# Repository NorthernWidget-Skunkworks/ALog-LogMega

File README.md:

ALog-LogMega
============

v. 0.8.3
rev 2

Arduino Mega (ATmega 2560) version of the ALog, designed to accomodate a larger numbers of sensors, break out a more significant set of 3.3V I/O pins, include switched VCC output, include headers for Arduino shields with switched power (e.g., for telemetry), break out SPI, I2C, and UART for communications with a wider range of sensors (and more reliable UART communications than the Software Serial library), and handle a much larger code base.

NOTE:
Gerbers out of date!
BoM out of date!

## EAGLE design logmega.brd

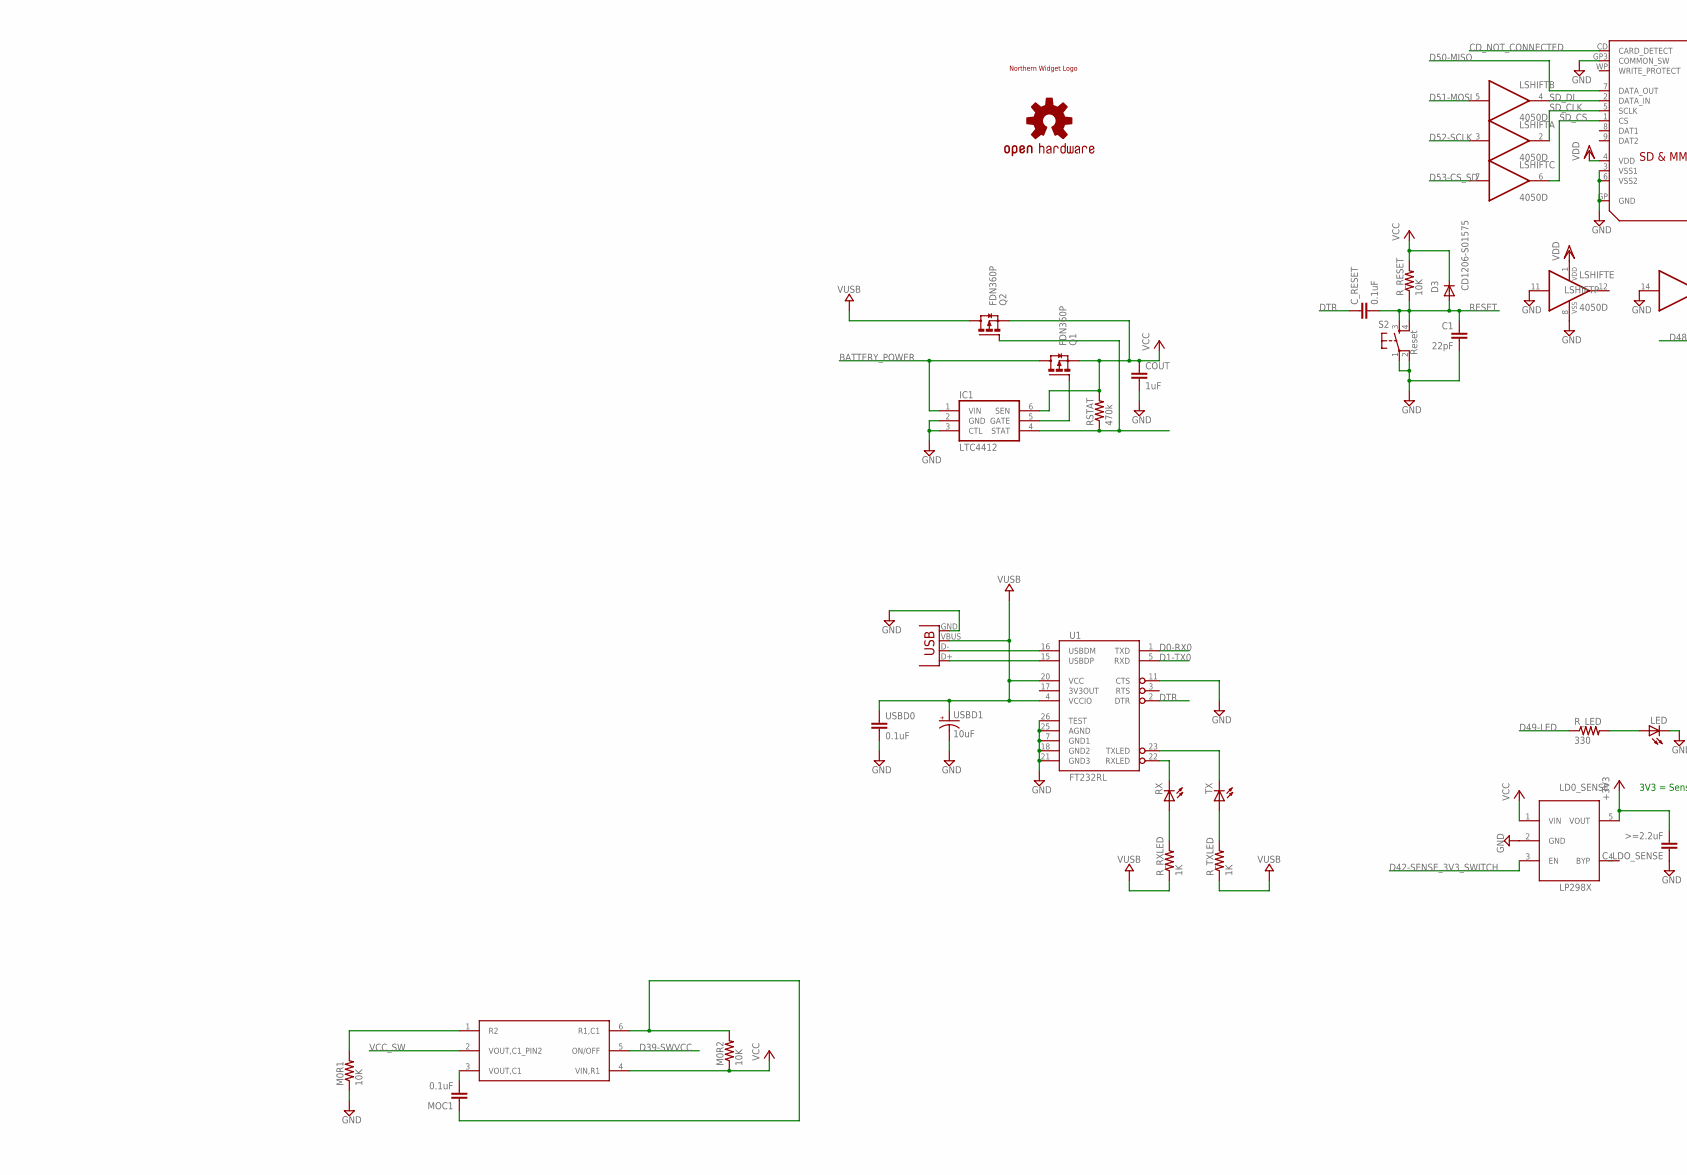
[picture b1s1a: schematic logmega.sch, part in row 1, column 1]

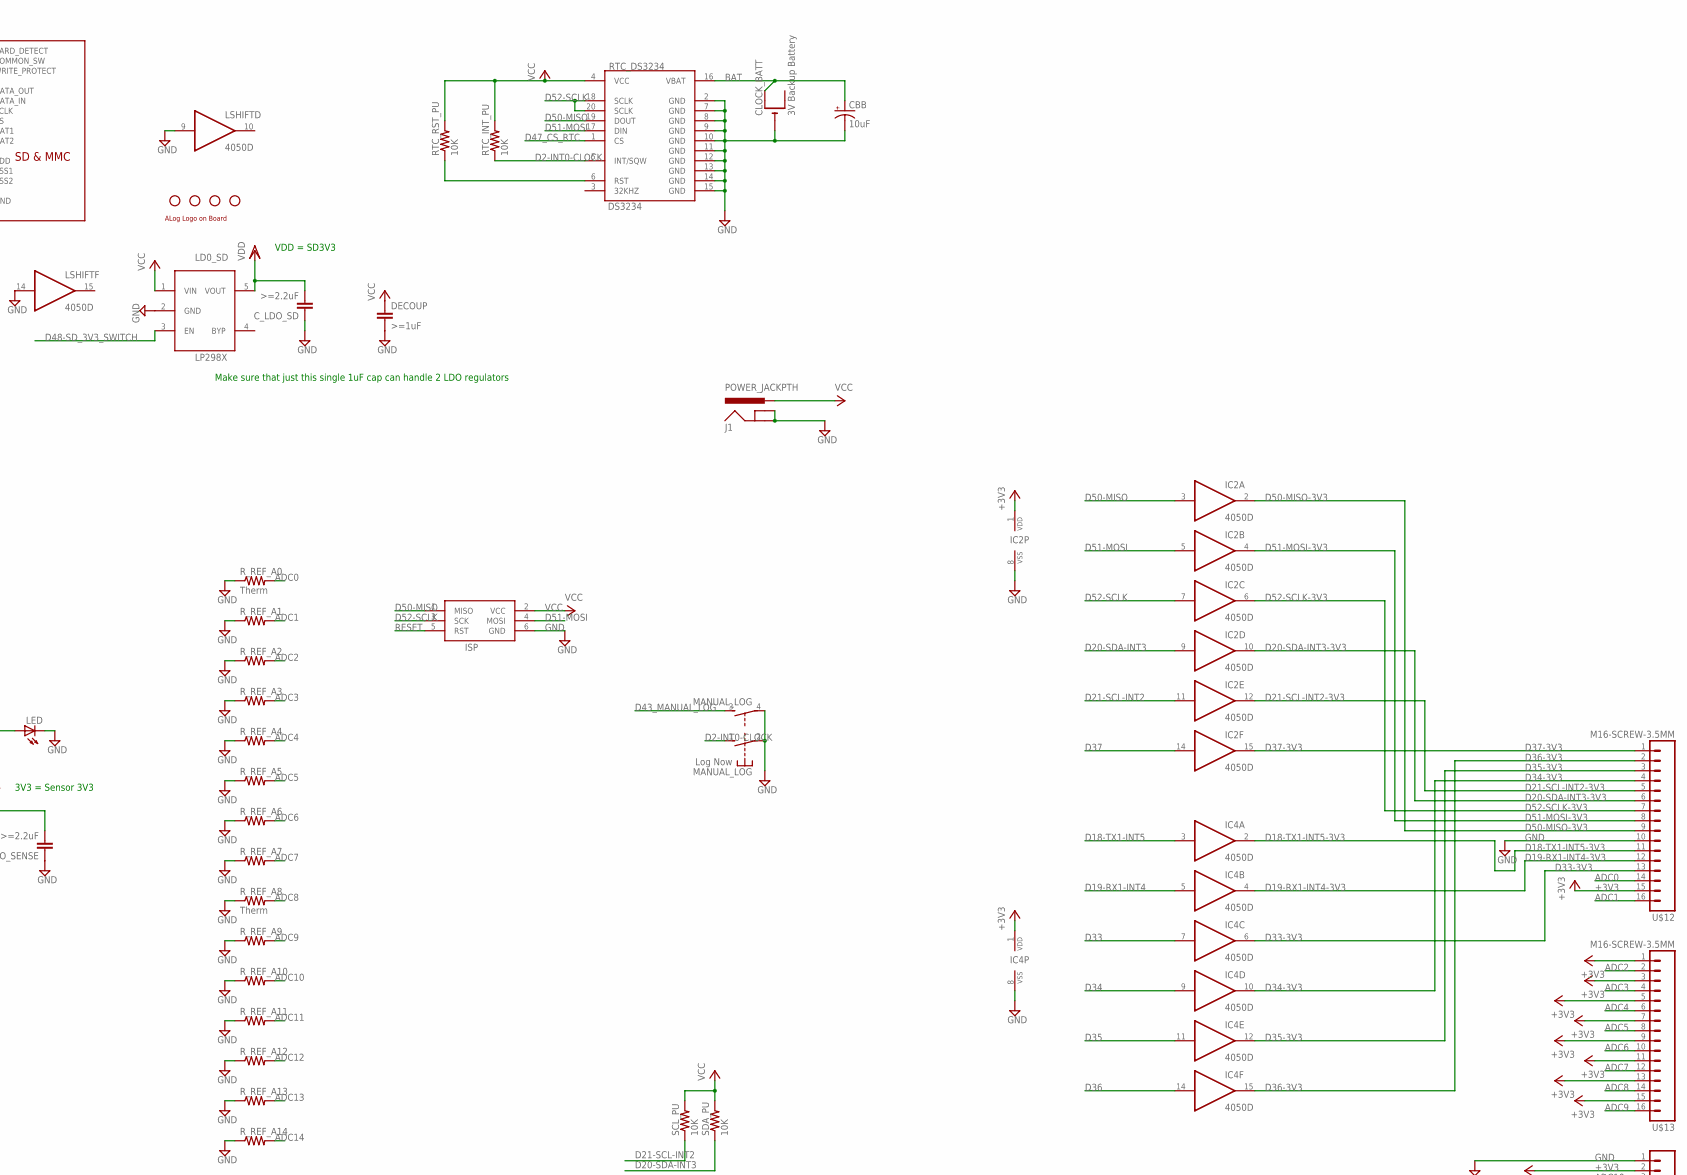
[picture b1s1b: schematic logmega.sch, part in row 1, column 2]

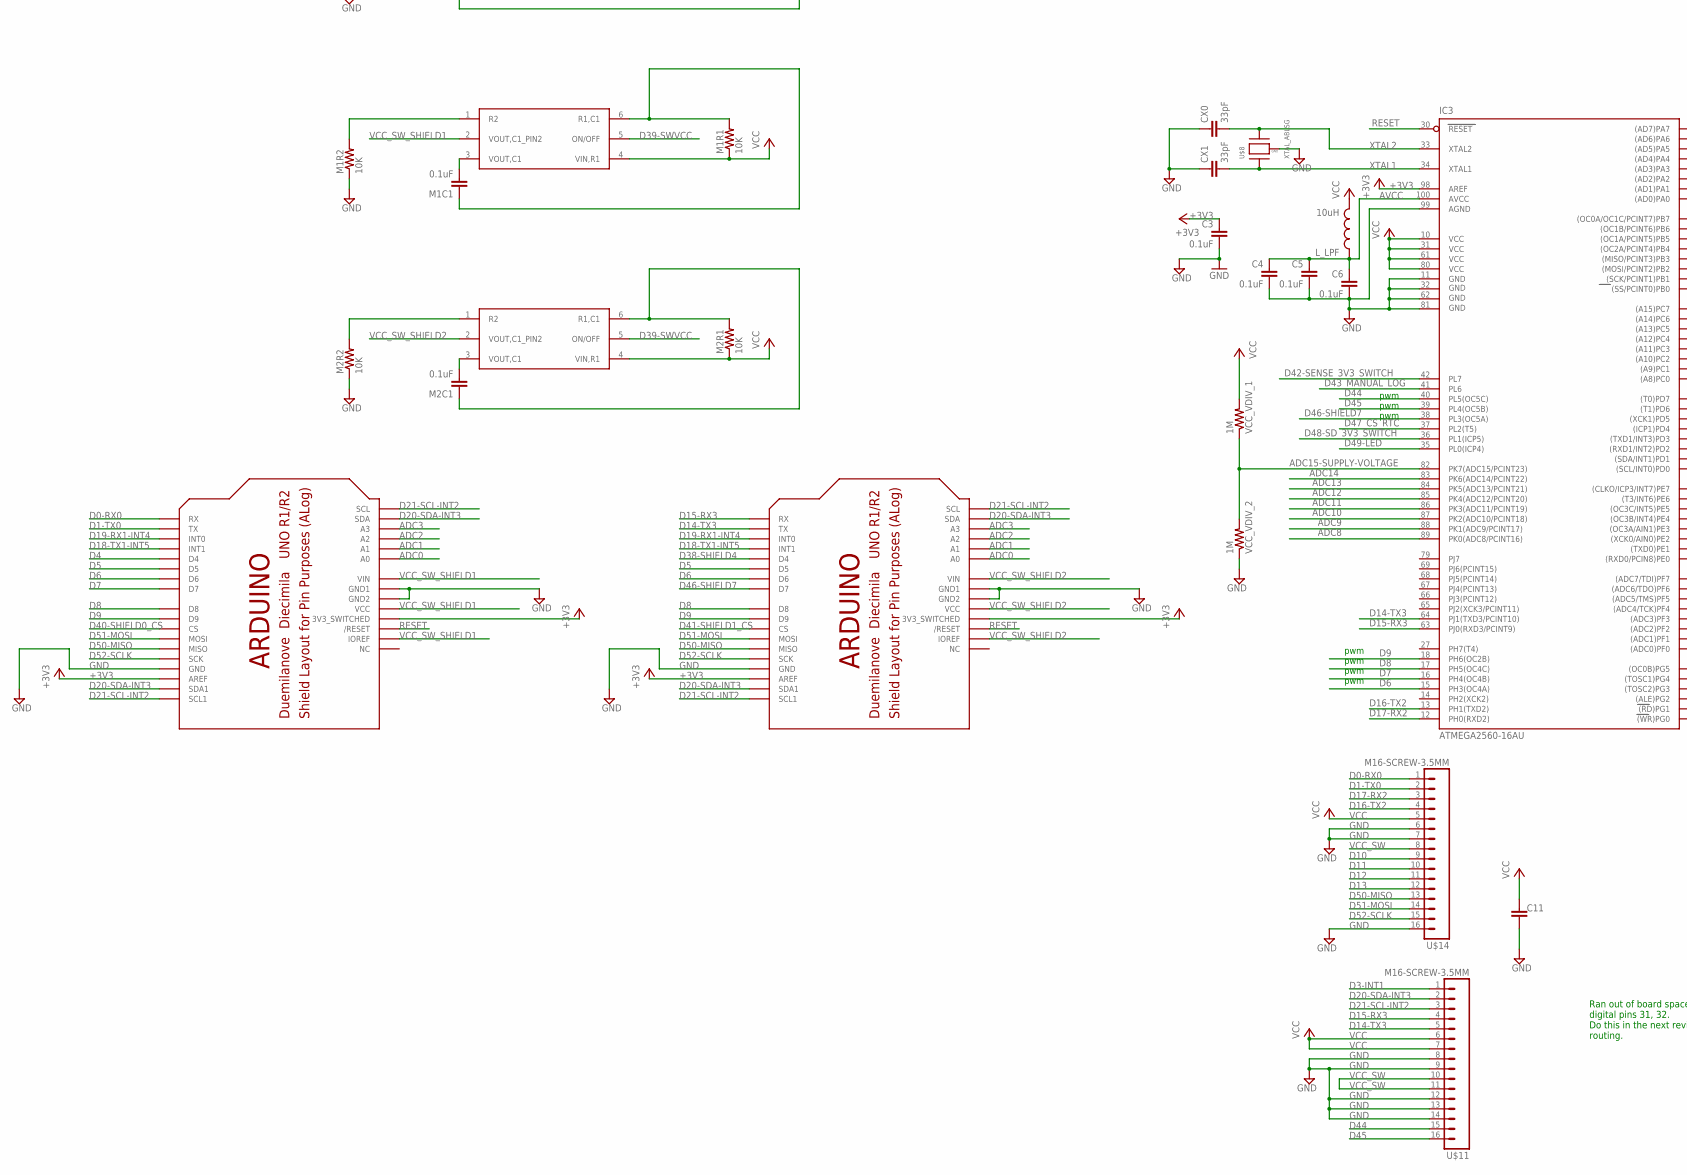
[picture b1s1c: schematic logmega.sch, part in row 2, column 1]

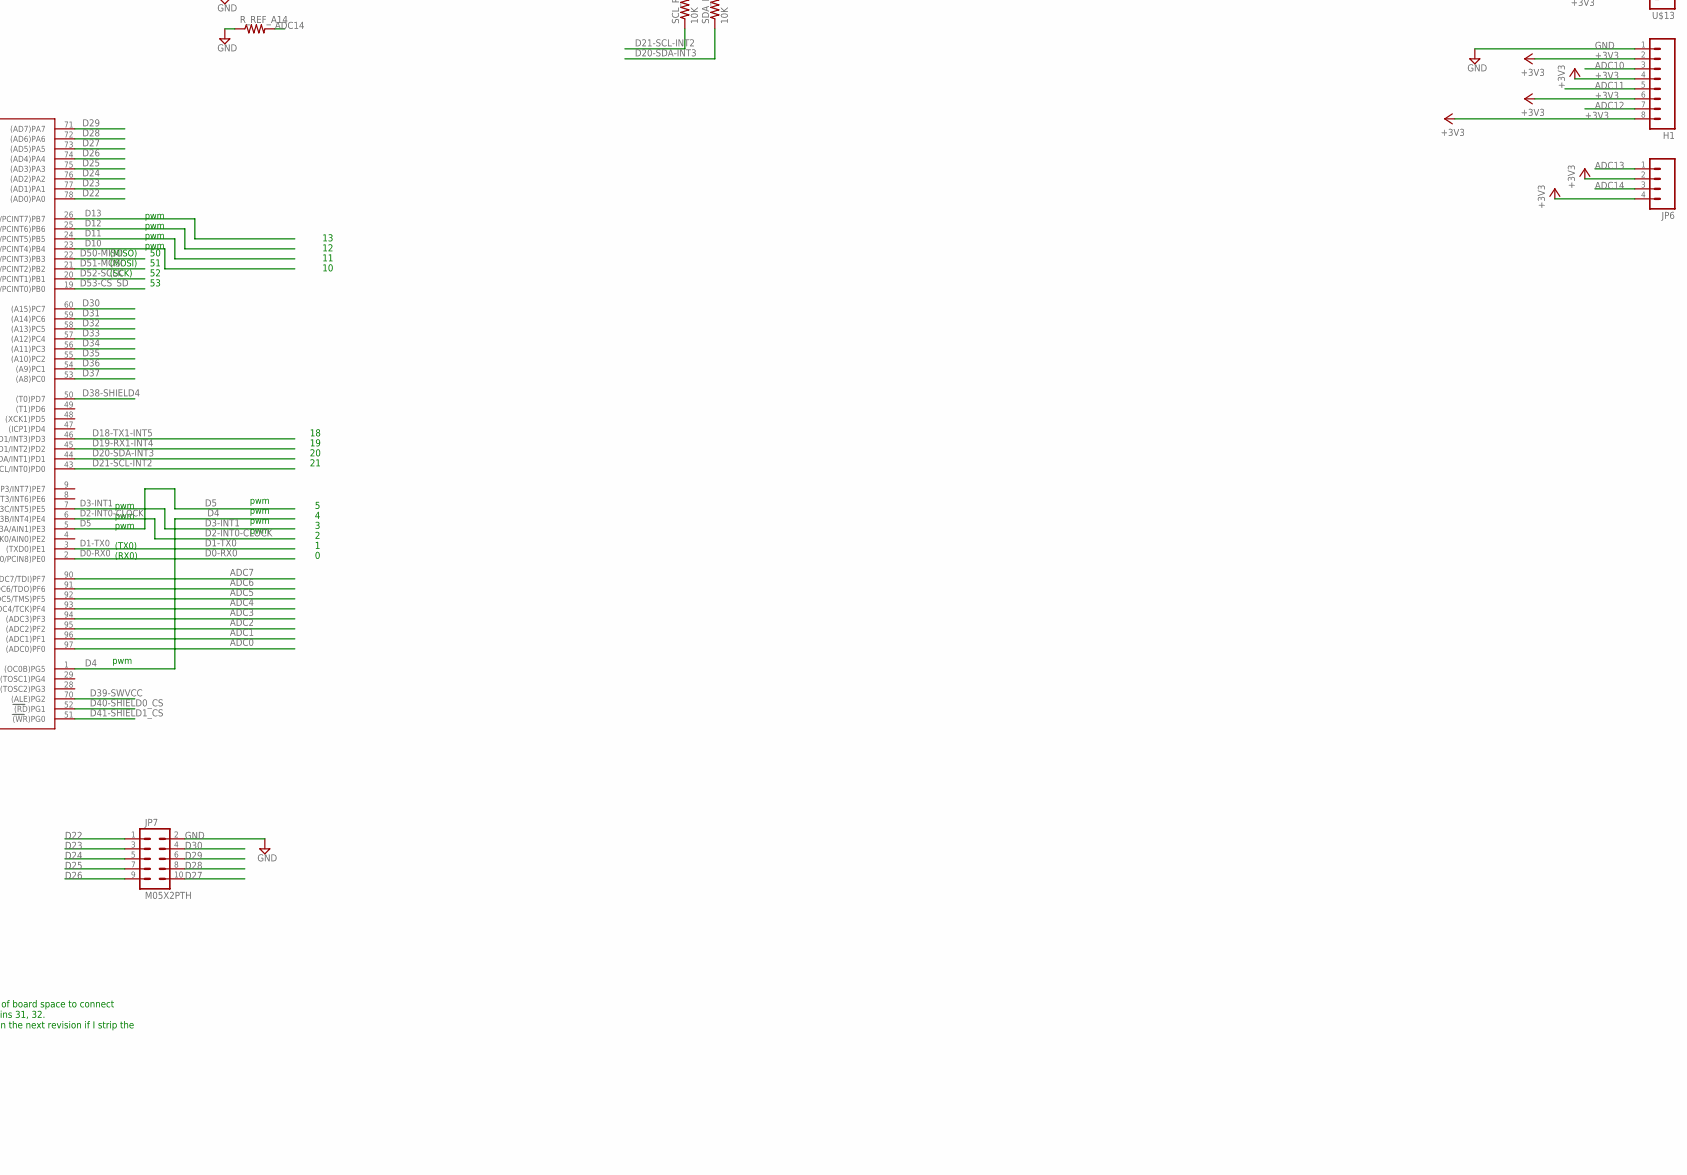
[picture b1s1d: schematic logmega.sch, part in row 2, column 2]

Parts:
C1: 22pF; C0603-ROUND
C3, C4, C5, C6, C11: 0.1uF; C0603-ROUND
CBB: 10uF; EIA3216
CLOCK_BATT: 3V Backup Battery; CR2032-SMD
COUT: 1uF; C0603-ROUND
CX0, CX1: 33pF; C0603
C_LDO_SD: >=2.2uF; C0603
C_LDO_SENSE: >=2.2uF; C0603
C_RESET: 0.1uF; C0603
D3: CD1206-S01575; MINIMELF
DECOUP: >=1uF; C0603
H1: M083.5MM-8; SCREWTERMINAL-3.5MM-8
IC1: LTC4412; TSOT23-6
IC2, IC4: 4050D; SO16
IC3: ATMEGA2560-16AU; TQFP100
ISP: AVRISP-6; AVRISP
J1: POWER_JACKPTH; POWER_JACK_PTH
JP1, JP2, JP3, JP4: STAND-OFF
JP5: USB-B; USB-B-PTH
JP6: M04SCREW; SCREWTERMINAL-3.5MM-4
JP7: M05X2PTH; AVR_ICSP
LD0_SD, LD0_SENSE: LP2985; SOT23-5L
LED: LED3MM
LOGO1: OSHW-LOGOM; OSHW-LOGO-M
LSHIFT: 4050D; SO16
L_LPF: 10uH; 0805
M0/SW, M1, M2: FDG6342L; SOT-363
M0R1, M0R2, M1R1, M1R2, M2R1, M2R2: 10K; R0603
M1C1, M2C1: 0.1uF; C0603
MANUAL_LOG: Log Now; PVA1F
MOC1: 0.1uF; C0603
Q1, Q2: FDN360P; SUPER-SOT3
RSTAT: 470k; R0603
RTC_DS3234: DS3234
RTC_INT_PU: 10K; R0603
RTC_RST_PU: 10K; R0603
RX: LED0603; LED-0603
R_LED: 330; R0603
R_REF_A0, R_REF_A8: Therm; 0207/10
R_REF_A1, R_REF_A2, R_REF_A3, R_REF_A4, R_REF_A5, R_REF_A6, R_REF_A7, R_REF_A9, R_REF_A10, R_REF_A11, R_REF_A12, R_REF_A13, R_REF_A14: R-US_0207/10; 0207/10
R_RESET: 10K; R0603
R_RXLED: 1K; R0603
R_TXLED: 1K; R0603
S2: Reset; TACTILE-PTH
SCL_PU: 10K; R0603
SD: SDMMC06132; 06132
SDA_PU: 10K; R0603
TX: LED0603; LED-0603
U1: FT232RL; SSOP28DB
U$1: NWLOGO
U$2: ALOG_LOGO_V1_5.5MM; ALOG_LOGO_V1_SMALL
U$7: ARDUINO_SHIELD_BIGLOG_2; ARDUINO_SHIELD_PO_BL2
U$8: XTAL_ABLSG; AT49
U$9: ARDUINO_SHIELD_BIGLOG_1; ARDUINO_SHIELD_PO_BL1
U$11, U$12, U$13, U$14: M16-SCREW-3.5MM
USBD0: 0.1uF; C0603
USBD1: 10uF; EIA3216
VCC_VDIV_1, VCC_VDIV_2: 1M; R0603

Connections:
+3V3: C3.1, C_LDO_SENSE.2, H1.2, H1.4, H1.6, H1.8, IC2.1 (VDD), IC3.98 (AREF), IC4.1 (VDD), JP6.2, JP6.4, LD0_SENSE.5 (VOUT), U$7.3.3V (3V3_SWITCHED), U$7.AREF, U$9.3.3V (3V3_SWITCHED), U$9.AREF, U$12.15, U$13.1, U$13.3, U$13.5, U$13.7, U$13.9, U$13.11, U$13.13, U$13.15
ADC0: IC3.97 ((ADC0)PF0), R_REF_A0.2, U$7.A0, U$9.A0, U$12.14
ADC1: IC3.96 ((ADC1)PF1), R_REF_A1.2, U$7.A1, U$9.A1, U$12.16
ADC2: IC3.95 ((ADC2)PF2), R_REF_A2.2, U$7.A2, U$9.A2, U$13.2
ADC3: IC3.94 ((ADC3)PF3), R_REF_A3.2, U$7.A3, U$9.A3, U$13.4
ADC4: IC3.93 ((ADC4/TCK)PF4), R_REF_A4.2, U$13.6
ADC5: IC3.92 ((ADC5/TMS)PF5), R_REF_A5.2, U$13.8
ADC6: IC3.91 ((ADC6/TDO)PF6), R_REF_A6.2, U$13.10
ADC7: IC3.90 ((ADC7/TDI)PF7), R_REF_A7.2, U$13.12
ADC8: IC3.89 (PK0(ADC8/PCINT16)), R_REF_A8.2, U$13.14
ADC9: IC3.88 (PK1(ADC9/PCINT17)), R_REF_A9.2, U$13.16
ADC10: H1.3, IC3.87 (PK2(ADC10/PCINT18)), R_REF_A10.2
ADC11: H1.5, IC3.86 (PK3(ADC11/PCINT19)), R_REF_A11.2
ADC12: H1.7, IC3.85 (PK4(ADC12/PCINT20)), R_REF_A12.2
ADC13: IC3.84 (PK5(ADC13/PCINT21)), JP6.1, R_REF_A13.2
ADC14: IC3.83 (PK6(ADC14/PCINT22)), JP6.3, R_REF_A14.2
ADC15-SUPPLY-VOLTAGE: IC3.82 (PK7(ADC15/PCINT23)), VCC_VDIV_1.1, VCC_VDIV_2.2
AVCC: C4.1, C5.1, C6.1, IC3.100 (AVCC), L_LPF.1
BAT: CBB.A (+), CLOCK_BATT.+$1 (+), RTC_DS3234.16 (VBAT)
BATTERY_POWER: IC1.1 (VIN), Q1.3 (D)
CD_NOT_CONNECTED: SD.CD (CARD_DETECT)
D0-RX0: IC3.2 ((RXD0/PCIN8)PE0), U1.1 (TXD), U$9.RX, U$14.1
D1-TX0: IC3.3 ((TXD0)PE1), U1.5 (RXD), U$9.TX, U$14.2
D2-INT0-CLOCK: IC3.6 ((OC3B/INT4)PE4), MANUAL_LOG.1 (S), RTC_DS3234.5 (INT/SQW), RTC_INT_PU.1
D3-INT1: IC3.7 ((OC3C/INT5)PE5), U$11.1
D4: IC3.1 ((OC0B)PG5), U$9.D4
D5: IC3.5 ((OC3A/AIN1)PE3), U$7.D5, U$9.D5
D6: IC3.15 (PH3(OC4A)), U$7.D6, U$9.D6
D7: IC3.16 (PH4(OC4B)), U$9.D7
D8: IC3.17 (PH5(OC4C)), U$7.D8, U$9.D8
D9: IC3.18 (PH6(OC2B)), U$7.D9, U$9.D9
D10: IC3.23 ((OC2A/PCINT4)PB4), U$14.9
D11: IC3.24 ((OC1A/PCINT5)PB5), U$14.10
D12: IC3.25 ((OC1B/PCINT6)PB6), U$14.11
D13: IC3.26 ((OC0A/OC1C/PCINT7)PB7), U$14.12
D14-TX3: IC3.64 (PJ1(TXD3/PCINT10)), U$7.TX, U$11.5
D15-RX3: IC3.63 (PJ0(RXD3/PCINT9)), U$7.RX, U$11.4
D16-TX2: IC3.13 (PH1(TXD2)), U$14.4
D17-RX2: IC3.12 (PH0(RXD2)), U$14.3
D18-TX1-INT5: IC3.46 ((TXD1/INT3)PD3), IC4.3 (I), U$7.D3 (INT1), U$9.D3 (INT1)
D18-TX1-INT5-3V3: IC4.2 (O), U$12.11
D19-RX1-INT4: IC3.45 ((RXD1/INT2)PD2), IC4.5 (I), U$7.D2 (INT0), U$9.D2 (INT0)
D19-RX1-INT4-3V3: IC4.4 (O), U$12.12
D20-SDA-INT3: IC2.9 (I), IC3.44 ((SDA/INT1)PD1), SDA_PU.1, U$7.A4 (SDA), U$7.SDA (SDA1), U$9.A4 (SDA), U$9.SDA (SDA1), U$11.2
D20-SDA-INT3-3V3: IC2.10 (O), U$12.6
D21-SCL-INT2: IC2.11 (I), IC3.43 ((SCL/INT0)PD0), SCL_PU.1, U$7.A5 (SCL), U$7.SCL (SCL1), U$9.A5 (SCL), U$9.SCL (SCL1), U$11.3
D21-SCL-INT2-3V3: IC2.12 (O), U$12.5
D22: IC3.78 ((AD0)PA0), JP7.1
D23: IC3.77 ((AD1)PA1), JP7.3
D24: IC3.76 ((AD2)PA2), JP7.5
D25: IC3.75 ((AD3)PA3), JP7.7
D26: IC3.74 ((AD4)PA4), JP7.9
D27: IC3.73 ((AD5)PA5), JP7.10
D28: IC3.72 ((AD6)PA6), JP7.8
D29: IC3.71 ((AD7)PA7), JP7.6
D30: IC3.60 ((A15)PC7), JP7.4
D31: IC3.59 ((A14)PC6)
D32: IC3.58 ((A13)PC5)
D33: IC3.57 ((A12)PC4), IC4.7 (I)
D33-3V3: IC4.6 (O), U$12.13
D34: IC3.56 ((A11)PC3), IC4.9 (I)
D34-3V3: IC4.10 (O), U$12.4
D35: IC3.55 ((A10)PC2), IC4.11 (I)
D35-3V3: IC4.12 (O), U$12.3
D36: IC3.54 ((A9)PC1), IC4.14 (I)
D36-3V3: IC4.15 (O), U$12.2
D37: IC2.14 (I), IC3.53 ((A8)PC0)
D37-3V3: IC2.15 (O), U$12.1
D38-SHIELD4: IC3.50 ((T0)PD7), U$7.D4
D39-SWVCC: IC3.70 ((ALE)PG2), M0/SW.5 (ON/OFF), M1.5 (ON/OFF), M2.5 (ON/OFF)
D40-SHIELD0_CS: IC3.52 ((RD)PG1), U$9.D10 (CS)
D41-SHIELD1_CS: IC3.51 ((WR)PG0), U$7.D10 (CS)
D42-SENSE_3V3_SWITCH: IC3.42 (PL7), LD0_SENSE.3 (EN)
D43_MANUAL_LOG: IC3.41 (PL6), MANUAL_LOG.3 (S)
D44: IC3.40 (PL5(OC5C)), U$11.15
D45: IC3.39 (PL4(OC5B)), U$11.16
D46-SHIELD7: IC3.38 (PL3(OC5A)), U$7.D7
D47_CS_RTC: IC3.37 (PL2(T5)), RTC_DS3234.1 (CS)
D48-SD_3V3_SWITCH: IC3.36 (PL1(ICP5)), LD0_SD.3 (EN)
D49-LED: IC3.35 (PL0(ICP4)), R_LED.1
D50-MISO: IC2.3 (I), IC3.22 ((MISO/PCINT3)PB3), ISP.1 (MISO), RTC_DS3234.19 (DOUT), SD.7 (DATA_OUT), U$7.D12 (MISO), U$9.D12 (MISO), U$14.13
D50-MISO-3V3: IC2.2 (O), U$12.9
D51-MOSI: IC2.5 (I), IC3.21 ((MOSI/PCINT2)PB2), ISP.4 (MOSI), LSHIFT.5 (I), RTC_DS3234.17 (DIN), U$7.D11 (MOSI), U$9.D11 (MOSI), U$14.14
D51-MOSI-3V3: IC2.4 (O), U$12.8
D52-SCLK: IC2.7 (I), IC3.20 ((SCK/PCINT1)PB1), ISP.3 (SCK), LSHIFT.3 (I), RTC_DS3234.18 (SCLK), RTC_DS3234.20 (SCLK), U$7.D13 (SCK), U$9.D13 (SCK), U$14.15
D52-SCLK-3V3: IC2.6 (O), U$12.7
D53-CS_SD: IC3.19 ((SS/PCINT0)PB0), LSHIFT.7 (I)
DTR: C_RESET.1, U1.2 (DTR)
GND: C1.2, C3.2, C4.2, C5.2, C6.2, C11.1, CBB.C (-), CLOCK_BATT.-, COUT.2, CX0.1, CX1.1, C_LDO_SD.1, C_LDO_SENSE.1, DECOUP.2, H1.1, IC1.2 (GND), IC1.3 (CTL), IC2.8 (VSS), IC3.11 (GND), IC3.32 (GND1), IC3.62 (GND2), IC3.81 (GND3), IC3.99 (AGND), IC4.8 (VSS), ISP.6 (GND), J1.GND, J1.GNDBREAK, JP5.GND, JP7.2, LD0_SD.2 (GND), LD0_SENSE.2 (GND), LED.K (C), LSHIFT.8 (VSS), LSHIFT.9 (I), LSHIFT.11 (I), LSHIFT.14 (I), M0R1.1, M1R2.1, M2R2.1, MANUAL_LOG.2, MANUAL_LOG.4, RTC_DS3234.2 (GND), RTC_DS3234.7 (GND), RTC_DS3234.8 (GND), RTC_DS3234.9 (GND), RTC_DS3234.10 (GND), RTC_DS3234.11 (GND), RTC_DS3234.12 (GND), RTC_DS3234.13 (GND), RTC_DS3234.14 (GND), RTC_DS3234.15 (GND), R_REF_A0.1, R_REF_A1.1, R_REF_A2.1, R_REF_A3.1, R_REF_A4.1, R_REF_A5.1, R_REF_A6.1, R_REF_A7.1, R_REF_A8.1, R_REF_A9.1, R_REF_A10.1, R_REF_A11.1, R_REF_A12.1, R_REF_A13.1, R_REF_A14.1, S2.1, S2.2, SD.3 (VSS1), SD.6 (VSS2), SD.GP (GND), SD.GP3 (COMMON_SW), U1.7 (GND1), U1.11 (CTS), U1.18 (GND2), U1.21 (GND3), U1.25 (AGND), U1.26 (TEST), U$7.GND@0 (GND), U$7.GND@1 (GND1), U$7.GND@2 (GND2), U$8.GND, U$9.GND@0 (GND), U$9.GND@1 (GND1), U$9.GND@2 (GND2), U$11.8, U$11.9, U$11.12, U$11.13, U$11.14, U$12.10, U$14.6, U$14.7, U$14.16, USBD0.2, USBD1.C (-), VCC_VDIV_2.1
LED+: LED.A, R_LED.2
unnamed: RX.C, U1.22 (RXLED)
unnamed: JP5.D+, U1.15 (USBDP)
unnamed: JP5.D-, U1.16 (USBDM)
unnamed: TX.C, U1.23 (TXLED)
unnamed: RX.A, R_RXLED.2
unnamed: R_TXLED.2, TX.A
unnamed: IC1.4 (STAT), Q2.1 (G), RSTAT.1
unnamed: IC1.5 (GATE), Q1.1 (G)
unnamed: RTC_DS3234.6 (RST), RTC_RST_PU.1
unnamed: M0/SW.3 (VOUT,C1), MOC1.2
unnamed: M1.1 (R2), M1R2.2
unnamed: M0/SW.1 (R2), M0R1.2
unnamed: M0/SW.6 (R1,C1), M0R2.2, MOC1.1
unnamed: M1.6 (R1,C1), M1C1.1, M1R1.2
unnamed: M1.3 (VOUT,C1), M1C1.2
unnamed: M2.1 (R2), M2R2.2
unnamed: M2.6 (R1,C1), M2C1.1, M2R1.2
unnamed: M2.3 (VOUT,C1), M2C1.2
RESET: C1.1, C_RESET.2, D3.A, IC3.30 (RESET), ISP.5 (RST), R_RESET.1, S2.3, S2.4, U$7.RES (/RESET), U$9.RES (/RESET)
SD_CLK: LSHIFT.2 (O), SD.5 (SCLK)
SD_CS: LSHIFT.6 (O), SD.1 (CS)
SD_DI: LSHIFT.4 (O), SD.2 (DATA_IN)
VCC: C11.2, COUT.1, D3.C, DECOUP.1, IC1.6 (SEN), IC3.10 (VCC), IC3.31 (VCC1), IC3.61 (VCC2), IC3.80 (VCC3), ISP.2 (VCC), J1.PWR, LD0_SD.1 (VIN), LD0_SENSE.1 (VIN), L_LPF.2, M0/SW.4 (VIN,R1), M0R2.1, M1.4 (VIN,R1), M1R1.1, M2.4 (VIN,R1), M2R1.1, Q1.2 (S), Q2.2 (S), RSTAT.2, RTC_DS3234.4 (VCC), RTC_INT_PU.2, RTC_RST_PU.2, R_RESET.2, SCL_PU.2, SDA_PU.2, U$11.6, U$11.7, U$14.5, VCC_VDIV_1.2
VCC_SW: M0/SW.2 (VOUT,C1_PIN2), U$11.10, U$11.11, U$14.8
VCC_SW_SHIELD1: M1.2 (VOUT,C1_PIN2), U$9.5V (VCC), U$9.IOREF, U$9.VIN
VCC_SW_SHIELD2: M2.2 (VOUT,C1_PIN2), U$7.5V (VCC), U$7.IOREF, U$7.VIN
VDD: C_LDO_SD.2, LD0_SD.5 (VOUT), LSHIFT.1 (VDD), SD.4 (VDD)
VUSB: JP5.VBUS, Q2.3 (D), R_RXLED.1, R_TXLED.1, U1.4 (VCCIO), U1.20 (VCC), USBD0.1, USBD1.A (+)
XTAL1: CX1.2, IC3.34 (XTAL1), U$8.IO1
XTAL2: CX0.2, IC3.33 (XTAL2), U$8.IO2

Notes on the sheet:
VDD = SD3V3
3V3 = Sensor 3V3
Make sure that just this single 1uF cap can handle 2 LDO regulators
pwm
(TX0)
(RX0)
(MISO)
(SCK)
(MOSI)
Ran out of board space to connect digital pins 31, 32. Do this in the next revision if I strip the routing.

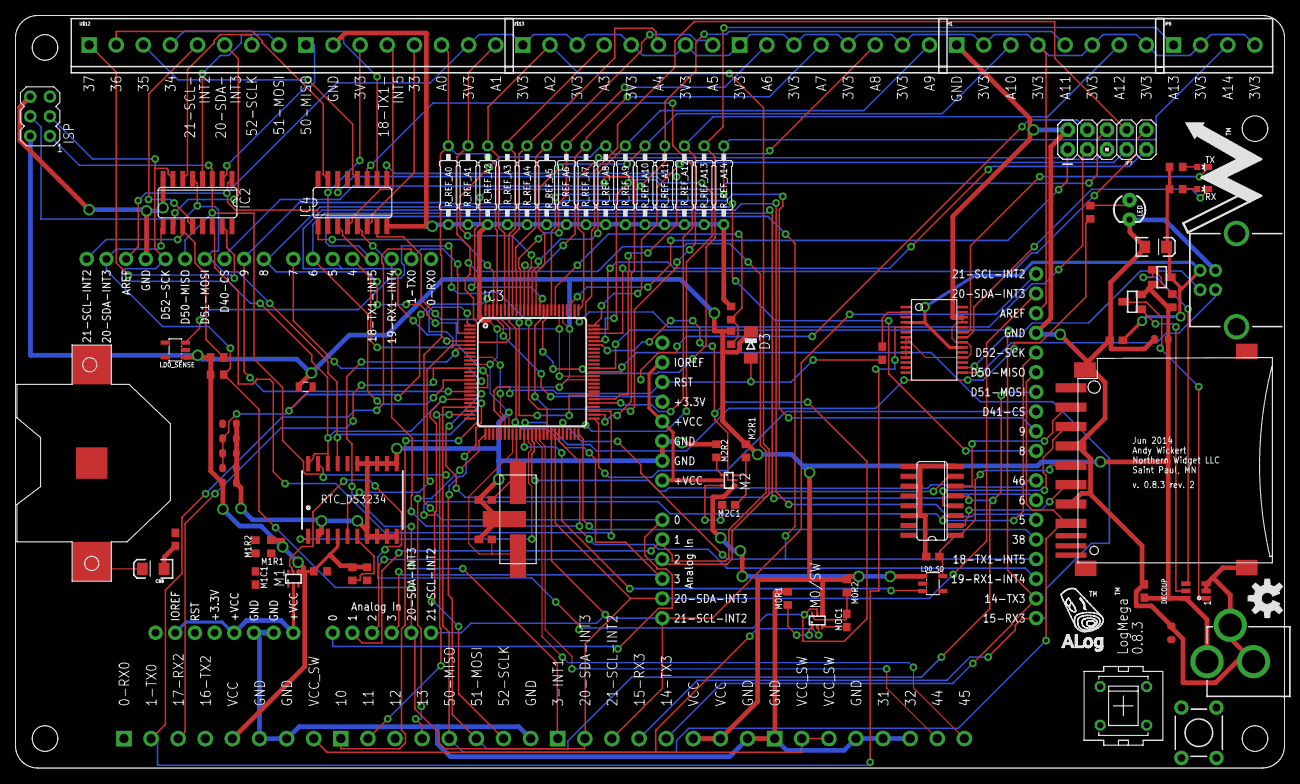
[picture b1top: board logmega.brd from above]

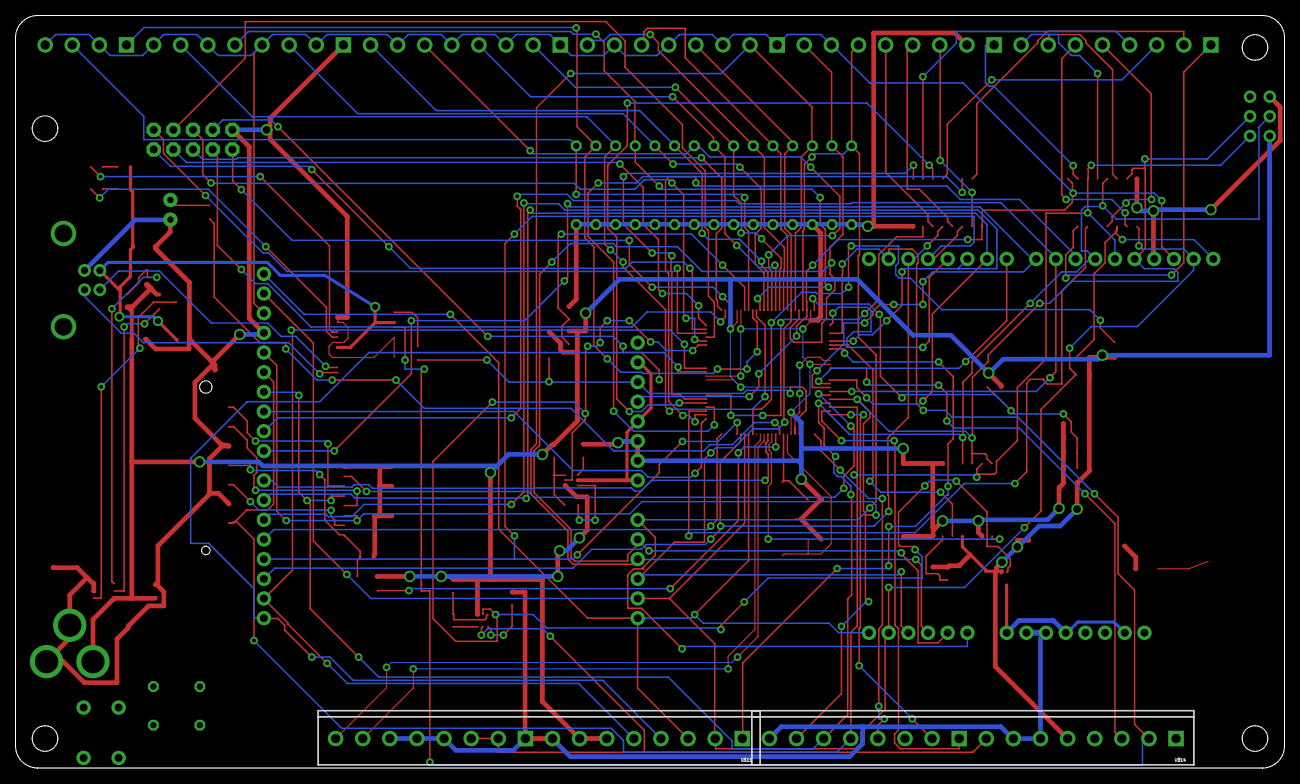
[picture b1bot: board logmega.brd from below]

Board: 2 copper layers, 163.8 x 97.2 mm, 94 parts (2 on the bottom side), 117 nets.

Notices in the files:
parts and their libraries:
SparkFun-DigitalIC: Licensing: CC v3.0 Share-Alike You are welcome to use this library for commercial purposes.
